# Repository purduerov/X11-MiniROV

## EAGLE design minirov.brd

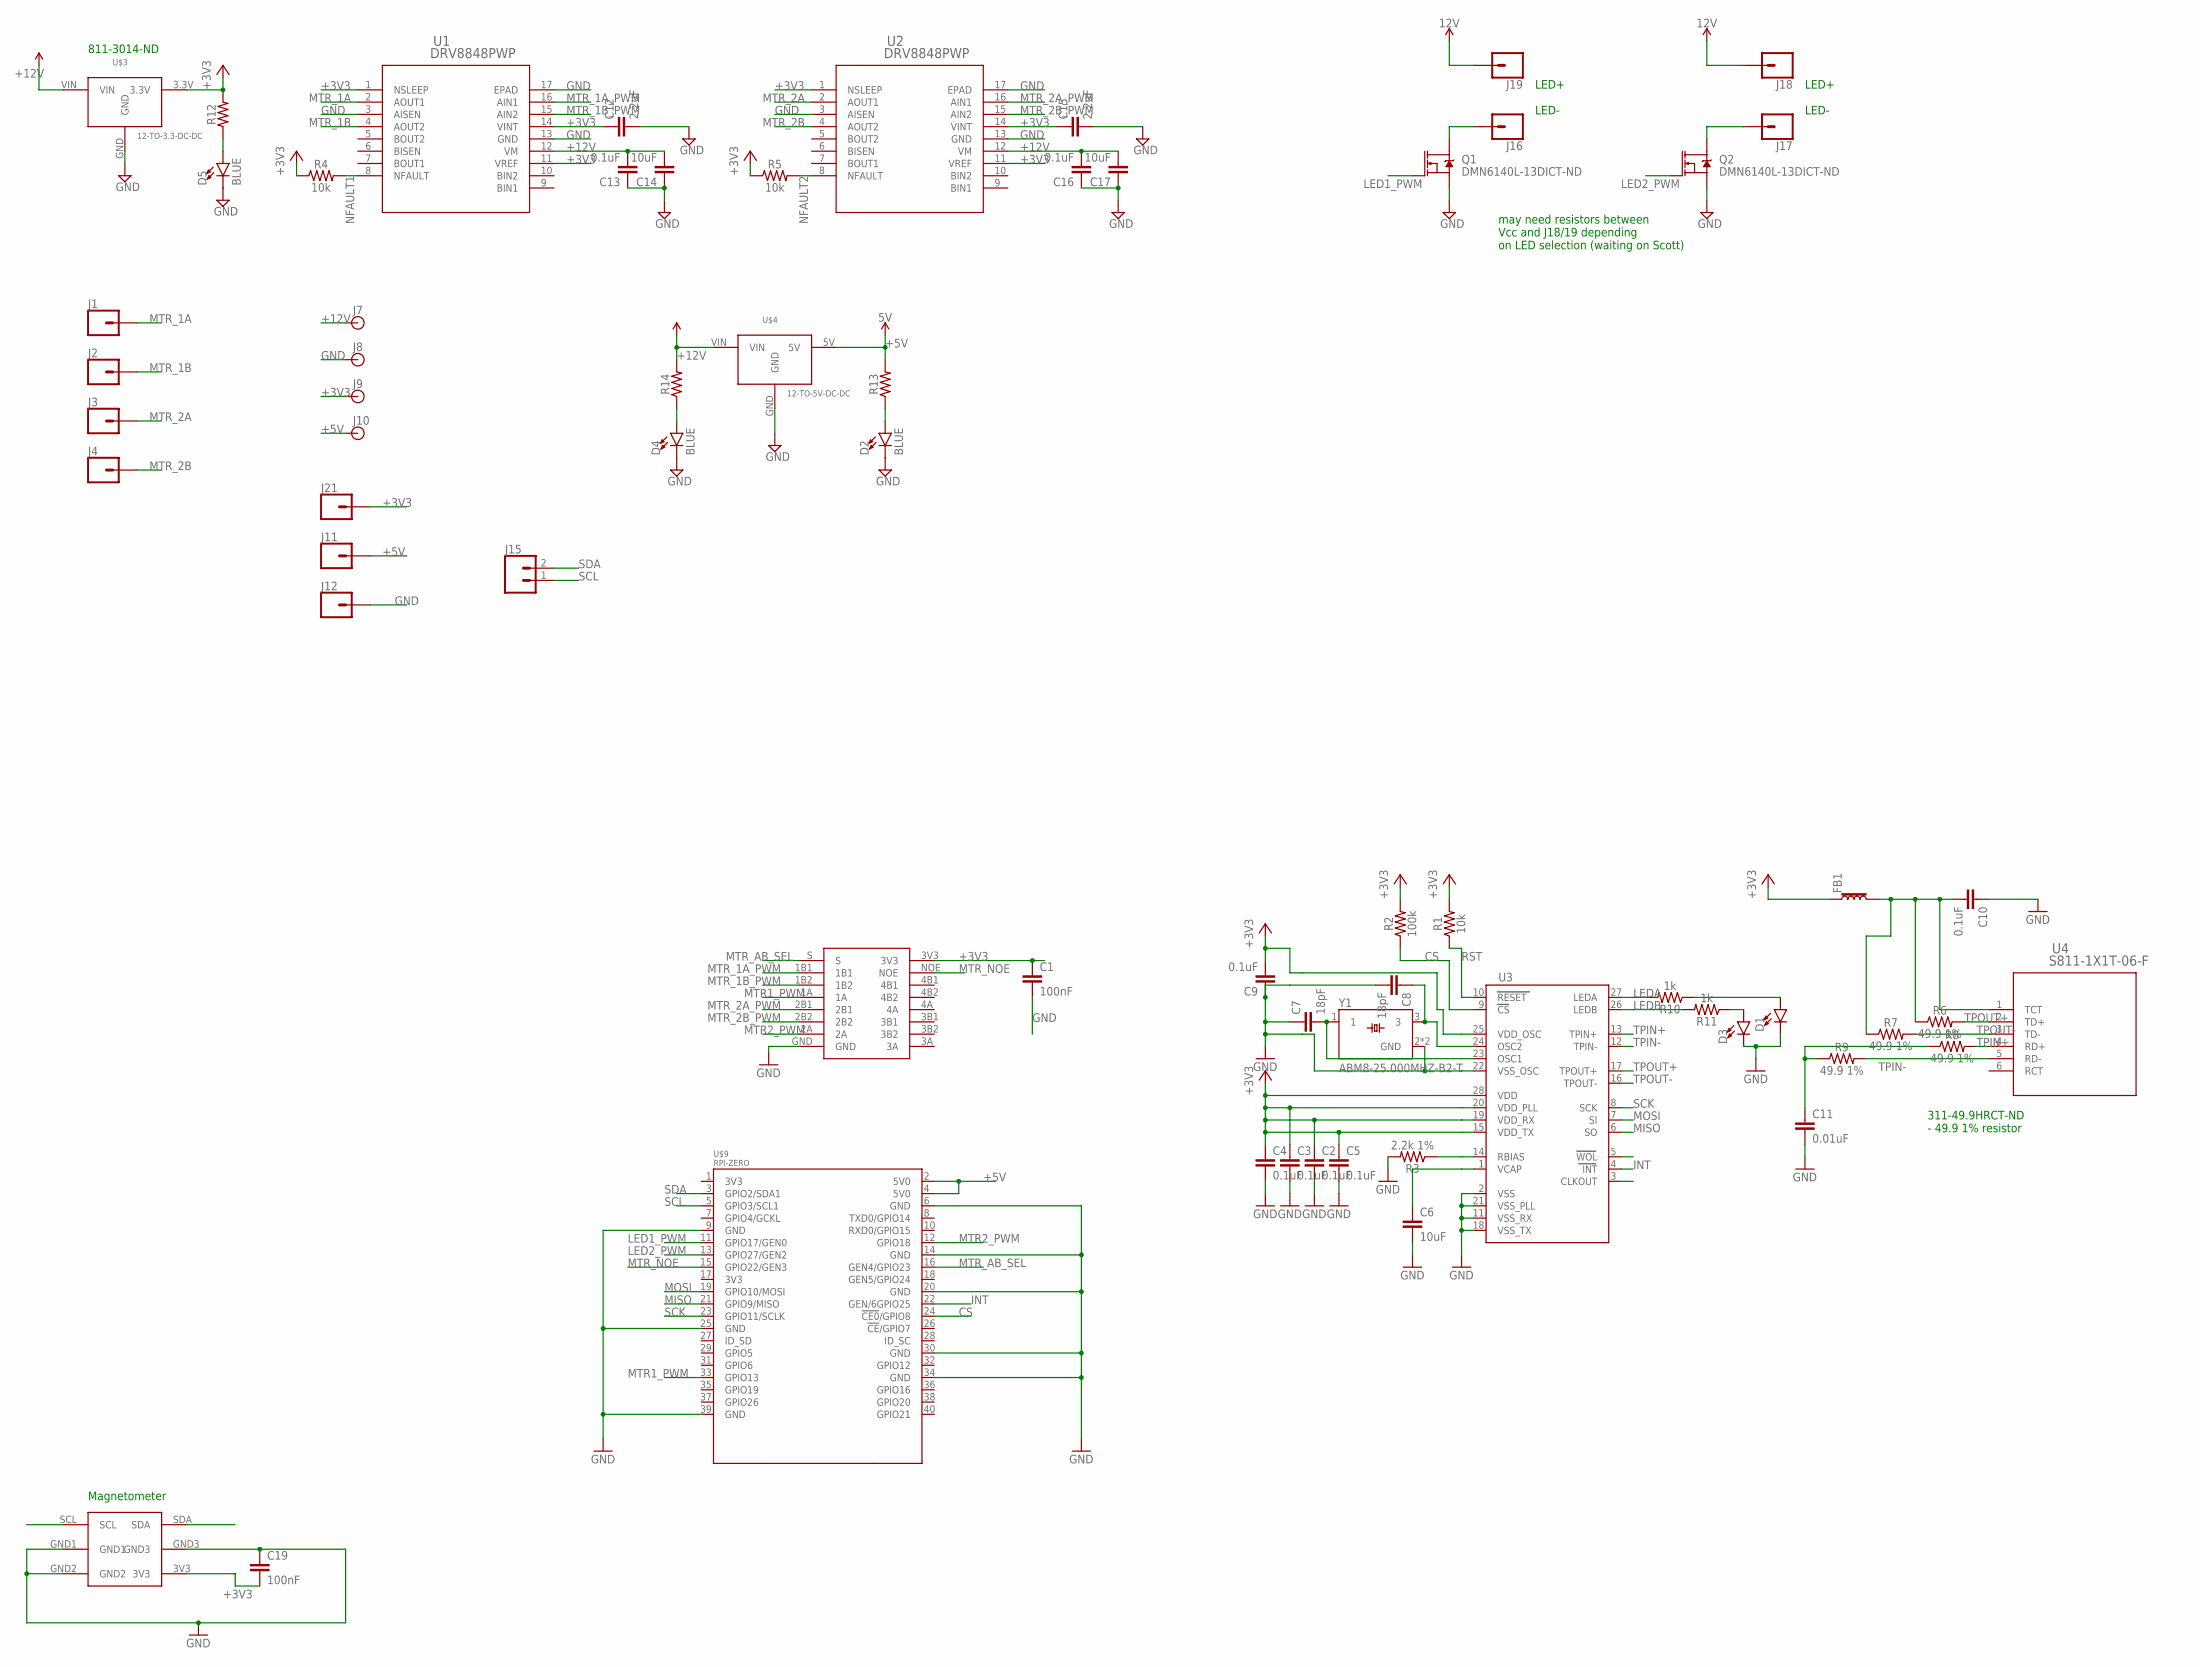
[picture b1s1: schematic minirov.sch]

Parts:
C1, C19: 100nF; 0603
C2, C3, C4, C5, C9, C10, C13, C16: 0.1uF; 0603
C6, C14, C17: 10uF; 0603
C7, C8: 18pF; 0603
C11: 0.01uF; 0603
C12, C15: 2.2uF; 0603
D1, D3: LED-BLUE0603; LED-0603
D2, D4, D5: BLUE; LED-0603
FB1: FERRITE_BEAD-0603; 0603
J1, J2, J3, J4, J11, J12, J16, J17, J18, J19, J21: CONN_01; 1X01
J7, J8, J9, J10: BANANA_CONN
J15: CONN_02; 1X02
Q1, Q2: DMN6140L-13DICT-ND; SOT23-3
R1, R4, R5: 10k; 0603
R2: 100k; 0603
R3: 2.2k 1%; 0603
R6, R7, R8, R9: 49.9 1%; 0603
R10, R11: 1k; 0603
R12, R13, R14: 0603
U1, U2: DRV8848PWP; PWP16_2P46X2P31
U3: ENC28J60; SSOP28DB
U4: S811-1X1T-06-F; S811-1X1T
U$2: 74CBTLV3257PW
U$3: 12-TO-3.3-DC-DC; MURATA-DCDC
U$4: 12-TO-5V-DC-DC; MURATA-DCDC_5V
U$8: TLE493DW2B6
U$9: RPI-ZERO; RASPBERRYPI_BASTELSTUBE_V13_RASPI_BOARD_B+_FULL
Y1: ABM8-25.000MHZ-B2-T; OSCSC320X250X100N

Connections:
+3V3: C1.1, C2.1, C3.1, C4.1, C5.1, C9.2, C12.1, C15.1, C19.2, FB1.1, J9.P$1, J21.1, R1.2, R2.2, R4.1, R5.1, R12.2, U1.1 (NSLEEP), U1.11 (VREF), U1.14 (VINT), U2.1 (NSLEEP), U2.11 (VREF), U2.14 (VINT), U3.15 (VDD_TX), U3.19 (VDD_RX), U3.20 (VDD_PLL), U3.25 (VDD_OSC), U3.28 (VDD), U$2.3V3, U$3.3.3V, U$8.3V3
+5V: J10.P$1, J11.1, R13.2, U$4.5V, U$9.2 (5V0), U$9.4 (5V0)
+12V: C13.2, C14.2, C16.2, C17.2, J7.P$1, J18.1, J19.1, R14.2, U1.12 (VM), U2.12 (VM), U$3.VIN, U$4.VIN
CS: R2.1, U3.9 (CS), U$9.24 (!CE0!/GPIO8)
GND: C1.2, C2.2, C3.2, C4.2, C5.2, C6.2, C7.1, C8.2, C9.1, C10.1, C11.2, C12.2, C13.1, C14.1, C15.2, C16.1, C17.1, C19.1, D1.C, D2.C, D3.C, D4.C, D5.C, J8.P$1, J12.1, Q1.2 (S), Q2.2 (S), R3.2, U1.3 (AISEN), U1.13 (GND), U1.17 (EPAD), U2.3 (AISEN), U2.13 (GND), U2.17 (EPAD), U3.2 (VSS), U3.11 (VSS_RX), U3.18 (VSS_TX), U3.21 (VSS_PLL), U3.22 (VSS_OSC), U$2.GND, U$3.GND, U$4.GND, U$8.GND1, U$8.GND2, U$8.GND3, U$9.6 (GND), U$9.9 (GND), U$9.14 (GND), U$9.20 (GND), U$9.25 (GND), U$9.30 (GND), U$9.34 (GND), U$9.39 (GND), Y1.2 (GND), Y1.4 (GND)
INT: U3.4 (INT), U$9.22 (GEN/6GPIO25)
LED1_PWM: Q1.1 (G), U$9.11 (GPIO17/GEN0)
LED2_PWM: Q2.1 (G), U$9.13 (GPIO27/GEN2)
LEDA: R10.2, U3.27 (LEDA)
LEDB: R11.2, U3.26 (LEDB)
MISO: U3.6 (SO), U$9.21 (GPIO9/MISO)
MOSI: U3.7 (SI), U$9.19 (GPIO10/MOSI)
MTR1_PWM: U$2.1A, U$9.33 (GPIO13)
MTR2_PWM: U$2.2A, U$9.12 (GPIO18)
MTR_1A: J1.1, U1.2 (AOUT1)
MTR_1A_PWM: U1.16 (AIN1), U$2.1B1
MTR_1B: J2.1, U1.4 (AOUT2)
MTR_1B_PWM: U1.15 (AIN2), U$2.1B2
MTR_2A: J3.1, U2.2 (AOUT1)
MTR_2A_PWM: U2.16 (AIN1), U$2.2B1
MTR_2B: J4.1, U2.4 (AOUT2)
MTR_2B_PWM: U2.15 (AIN2), U$2.2B2
MTR_AB_SEL: U$2.S, U$9.16 (GEN4/GPIO23)
MTR_NOE: U$2.NOE, U$9.15 (GPIO22/GEN3)
unnamed: C7.2, U3.23 (OSC1), Y1.1
unnamed: C8.1, U3.24 (OSC2), Y1.3
unnamed: D5.A, R12.1
unnamed: D1.A, R10.1
unnamed: D3.A, R11.1
unnamed: J17.1, Q2.3 (D)
unnamed: J16.1, Q1.3 (D)
unnamed: D2.A, R13.1
unnamed: D4.A, R14.1
unnamed: R3.1, U3.14 (RBIAS)
unnamed: C6.1, U3.1 (VCAP)
unnamed: C10.2, FB1.2, R6.1, R7.1, U4.1 (TCT)
unnamed: C11.1, R8.1, R9.1
NFAULT1: R4.2, U1.8 (NFAULT)
NFAULT2: R5.2, U2.8 (NFAULT)
RST: R1.1, U3.10 (RESET)
SCK: U3.8 (SCK), U$9.23 (GPIO11/SCLK)
SCL: J15.1, U$8.SCL, U$9.5 (GPIO3/SCL1)
SDA: J15.2, U$8.SDA, U$9.3 (GPIO2/SDA1)
TPIN+: R8.2, U3.13 (TPIN+), U4.4 (RD+)
TPIN-: R9.2, U3.12 (TPIN-), U4.5 (RD-)
TPOUT+: R6.2, U3.17 (TPOUT+), U4.2 (TD+)
TPOUT-: R7.2, U3.16 (TPOUT-), U4.3 (TD-)

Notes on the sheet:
811-3014-ND
may need resistors between Vcc and J18/19 depending on LED selection (waiting on Scott)
LED+ LED-
Magnetometer
311-49.9HRCT-ND - 49.9 1% resistor

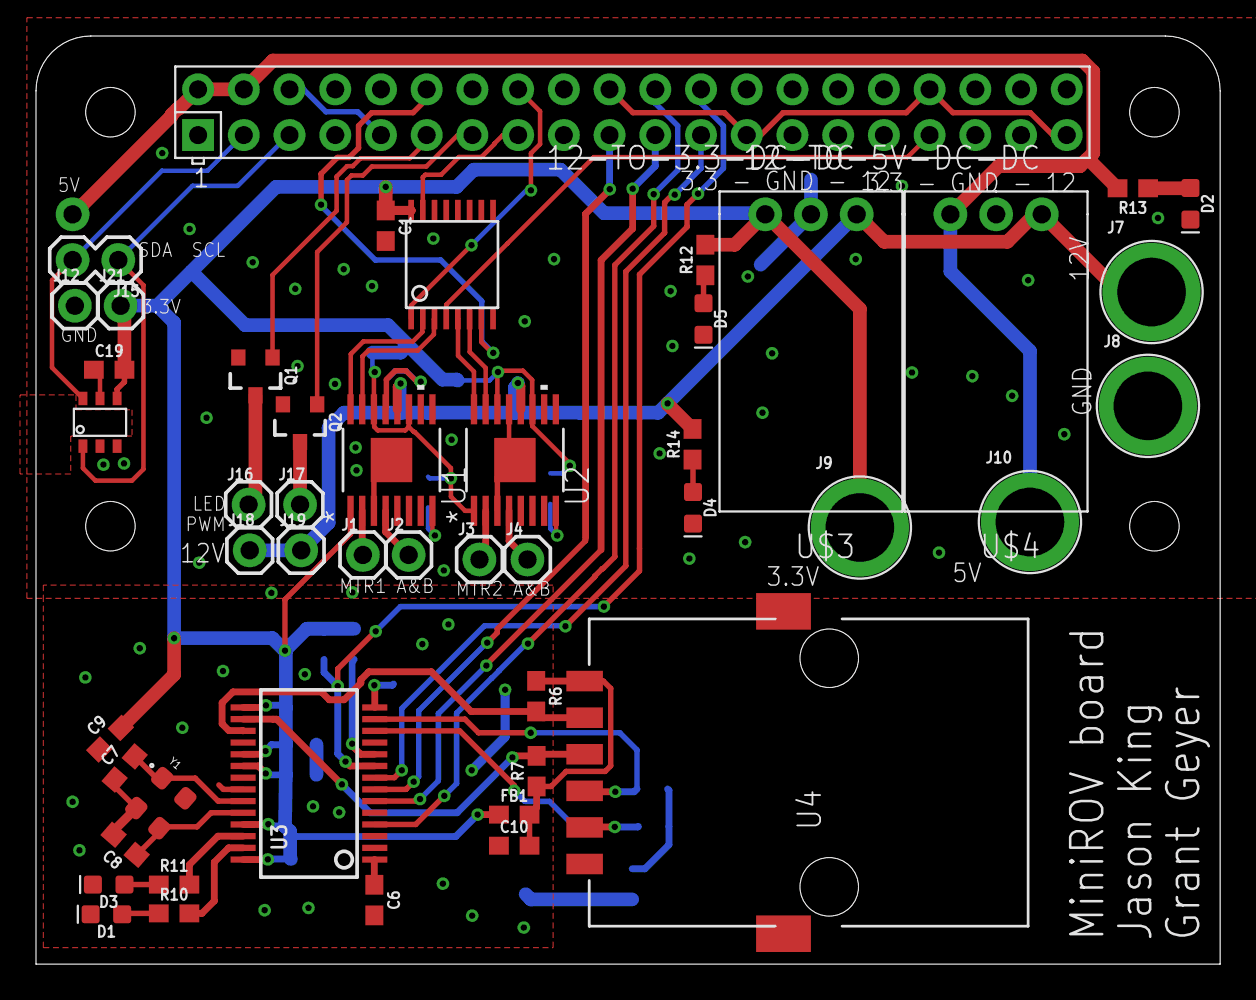
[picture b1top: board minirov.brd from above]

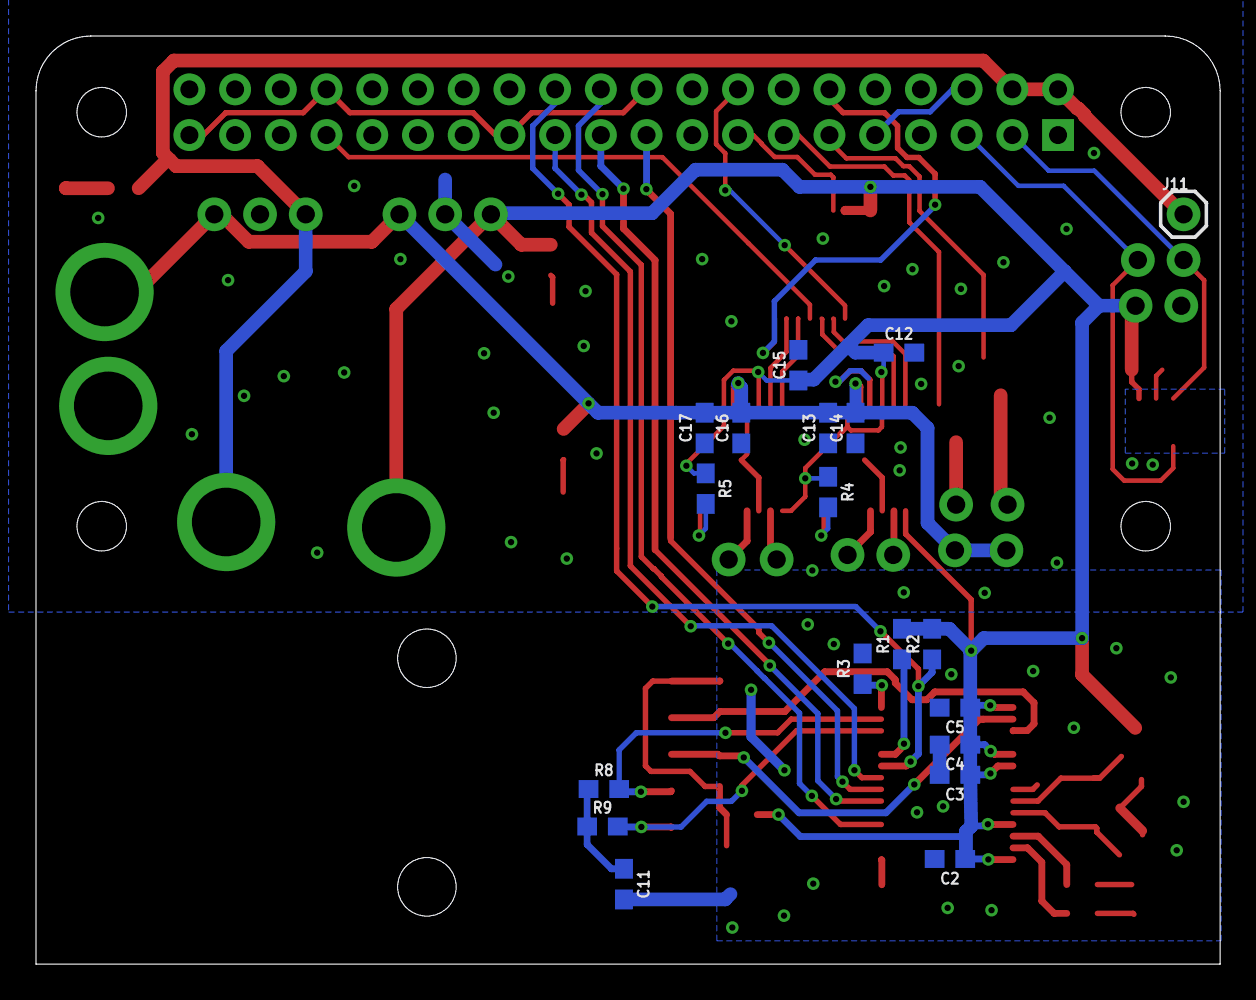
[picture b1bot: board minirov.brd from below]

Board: 2 copper layers, 65.8 x 51.6 mm, 66 parts (19 on the bottom side), 47 nets.

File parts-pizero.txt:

Partlist

Exported from minirov.brd at 1/16/2019 7:33 PM

EAGLE Version 9.1.3 Copyright (c) 1988-2018 Autodesk, Inc.

Assembly variant: 

Part     Value              Package                                         Library             Position (mil)        Orientation

C1       100nF              0603                                            SparkFun-Capacitors (765 795)             R270
C12      2.2uF              0603                                            SparkFun-Capacitors (702.5 517.5)         MR0
C13      0.1uF              0603                                            SparkFun-Capacitors (857.5 352.5)         MR90
C14      10uF               0603                                            SparkFun-Capacitors (797.5 352.5)         MR90
C15      2.2uF              0603                                            SparkFun-Capacitors (922.5 490)           MR90
C16      0.1uF              0603                                            SparkFun-Capacitors (1047.5 352.5)        MR90
C17      10uF               0603                                            SparkFun-Capacitors (1127.5 352.5)        MR90
C19      100nF              0603                                            SparkFun-Capacitors (160 480)             R0
J1                          1X01                                            SparkFun-Connectors (715 75)              R0
J2                          1X01                                            SparkFun-Connectors (815 75)              R0
J3                          1X01                                            SparkFun-Connectors (970 65)              R0
J4                          1X01                                            SparkFun-Connectors (1075 65)             R0
J7                          BANANA_CONN                                     SparkFun-Connectors (2440 650)            R0
J8                          BANANA_CONN                                     SparkFun-Connectors (1900 150)            R0
J9                          BANANA_CONN                                     SparkFun-Connectors (2160 150)            R0
J10                         BANANA_CONN                                     SparkFun-Connectors (2450 400)            R0
J11                         1X01                                            SparkFun-Connectors (80 820)              MR0
J12                         1X01                                            SparkFun-Connectors (85 620)              R0
J15                         1X02                                            SparkFun-Connectors (180 720)             R180
J16                         1X01                                            SparkFun-Connectors (465 185)             R0
J17                         1X01                                            SparkFun-Connectors (577.5 185)           R0
J18                         1X01                                            SparkFun-Connectors (467.5 85)            R0
J19                         1X01                                            SparkFun-Connectors (580 85)              R0
J21                         1X01                                            SparkFun-Connectors (185 620)             R0
Q1       DMN6140L-13DICT-ND SOT23-3                                         minirov             (480 467.5)           R180
Q2       DMN6140L-13DICT-ND SOT23-3                                         minirov             (577.5 365)           R180
R4       10k                0603                                            SparkFun-Resistors  (857.5 212.5)         MR270
R5       10k                0603                                            SparkFun-Resistors  (1125 220)            MR270
U$2      74CBTLV3257PW      74CBTLV3257PW                                   74CBTLV3257PW       (910 710)             R0
U$3      12-TO-3.3-DC-DC    MURATA-DCDC                                     minirov             (1695 820)            R180
U$4      12-TO-5V-DC-DC     MURATA-DCDC_5V                                  minirov             (2100 820)            R180
U$8      TLE493DW2B6        TLE493DW2B6                                     TLE493DW2B6         (140 365)             R0
U$9      RPI-ZERO           RASPBERRYPI_BASTELSTUBE_V13_RASPI_BOARD_B+_FULL RPI-Zero            (25 0)                R0
U1       DRV8848PWP         PWP16_2P46X2P31                                 minirov             (777.5 282.5)         R90
U2       DRV8848PWP         PWP16_2P46X2P31                                 minirov             (1047.5 282.5)        R90

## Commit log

2019-01-02 Initial version on git
2019-01-05 first iteration of schematic and board placements
2019-01-06 minor changes
2019-01-06 first round of routing. need to gnd stitch
2019-01-07 added ADC
2019-01-08 schematic changes and board changes to reflect it
2019-01-08 noted that GND stitching isn't done
2019-01-08 routing, deleting extraneous, and graphic
2019-01-16 misc changes
2019-01-17 added parts lists
2019-02-03 Changes i forgot to push
2019-02-03 routing
2019-02-04 couple checks and fixes
2019-02-05 Cleaned up routing, moved some connectors
2019-02-05 labels and ground stitching
2019-02-05 fixed airwire
2019-02-05 last airwire and a DRC check

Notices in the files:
parts and their libraries:
SparkFun-Capacitors: Licensing: Creative Commons ShareAlike 4.0 International - https://creativecommons.org/licenses/by-sa/4.0
microbuilder: This work is placed in the public domain, and may be freely used for commercial and non-commercial work with the following conditions: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
